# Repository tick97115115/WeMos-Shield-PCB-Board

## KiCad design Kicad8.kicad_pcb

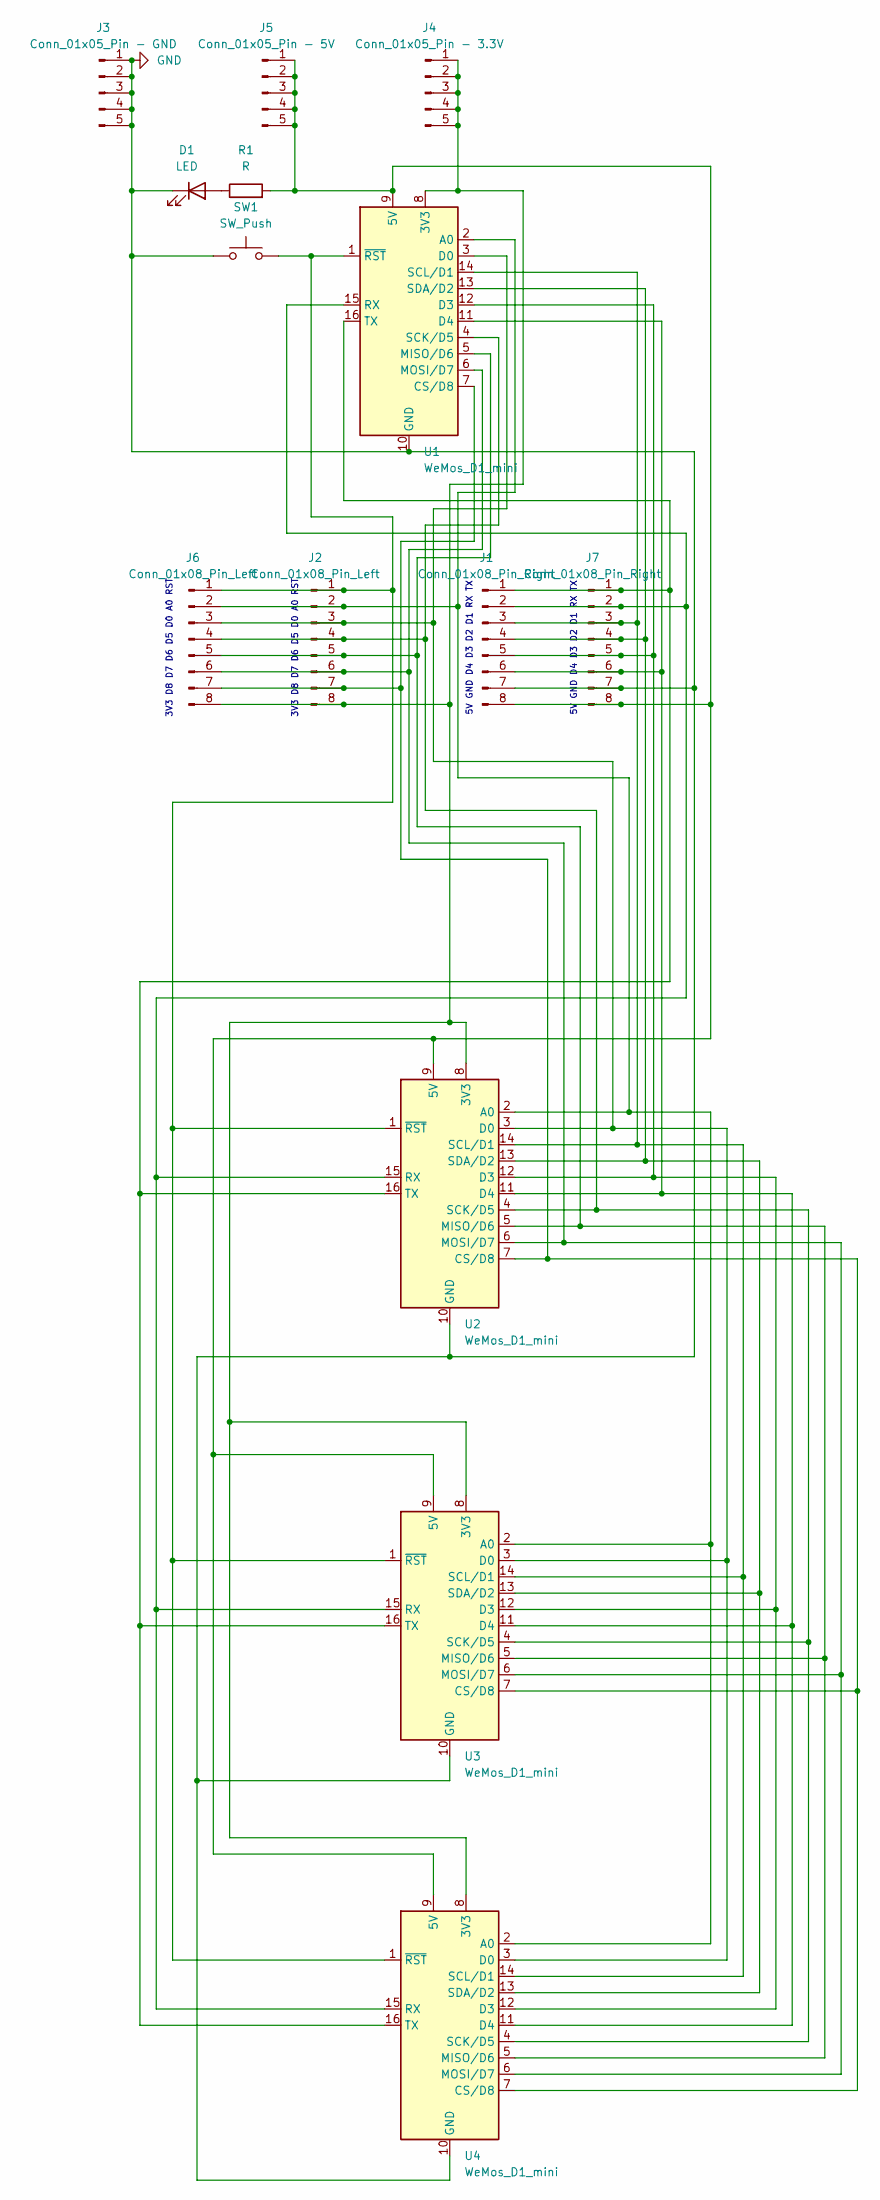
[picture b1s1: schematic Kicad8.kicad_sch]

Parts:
D1: LED; LED_D3.0mm
J1: Conn_01x08_Pin_Right; PinHeader_1x08_P2.54mm_Vertical
J2: Conn_01x08_Pin_Left; PinHeader_1x08_P2.54mm_Vertical
J3: Conn_01x05_Pin - GND; PinSocket_1x05_P2.54mm_Vertical
J4: Conn_01x05_Pin - 3.3V; PinSocket_1x05_P2.54mm_Vertical
J5: Conn_01x05_Pin - 5V; PinSocket_1x05_P2.54mm_Vertical
J6: Conn_01x08_Pin_Left; TerminalBlock_RND_205-00018_1x08_P5.00mm_Horizontal
J7: Conn_01x08_Pin_Right; TerminalBlock_RND_205-00018_1x08_P5.00mm_Horizontal
R1: R; R_Axial_DIN0207_L6.3mm_D2.5mm_P7.62mm_Horizontal
SW1: SW_Push; SW_PUSH_6mm_H5mm
U1, U2, U3, U4: WeMos_D1_mini; WEMOS_D1_mini_light

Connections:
GND: D1.1 (K), J1.7, J3.1, J3.2, J3.3, J3.4, J3.5, J7.7, SW1.1, U1.10 (GND), U2.10 (GND), U3.10 (GND), U4.10 (GND)
unnamed: D1.2 (A), R1.1
unnamed: J1.1, J7.1, U1.16 (TX), U2.16 (TX), U3.16 (TX), U4.16 (TX)
unnamed: J1.2, J7.2, U1.15 (RX), U2.15 (RX), U3.15 (RX), U4.15 (RX)
unnamed: J1.3, J7.3, U1.14 (SCL/D1), U2.14 (SCL/D1), U3.14 (SCL/D1), U4.14 (SCL/D1)
unnamed: J1.4, J7.4, U1.13 (SDA/D2), U2.13 (SDA/D2), U3.13 (SDA/D2), U4.13 (SDA/D2)
unnamed: J1.5, J7.5, U1.12 (D3), U2.12 (D3), U3.12 (D3), U4.12 (D3)
unnamed: J1.6, J7.6, U1.11 (D4), U2.11 (D4), U3.11 (D4), U4.11 (D4)
unnamed: J1.8, J5.1, J5.2, J5.3, J5.4, J5.5, J7.8, R1.2, U1.9 (5V), U2.9 (5V), U3.9 (5V), U4.9 (5V)
unnamed: J2.1, J6.1, SW1.2, U1.1 (~RST), U2.1 (~RST), U3.1 (~RST), U4.1 (~RST)
unnamed: J2.2, J6.2, U1.2 (A0), U2.2 (A0), U3.2 (A0), U4.2 (A0)
unnamed: J2.3, J6.3, U1.3 (D0), U2.3 (D0), U3.3 (D0), U4.3 (D0)
unnamed: J2.4, J6.4, U1.4 (SCK/D5), U2.4 (SCK/D5), U3.4 (SCK/D5), U4.4 (SCK/D5)
unnamed: J2.5, J6.5, U1.5 (MISO/D6), U2.5 (MISO/D6), U3.5 (MISO/D6), U4.5 (MISO/D6)
unnamed: J2.6, J6.6, U1.6 (MOSI/D7), U2.6 (MOSI/D7), U3.6 (MOSI/D7), U4.6 (MOSI/D7)
unnamed: J2.7, J6.7, U1.7 (CS/D8), U2.7 (CS/D8), U3.7 (CS/D8), U4.7 (CS/D8)
unnamed: J2.8, J4.1, J4.2, J4.3, J4.4, J4.5, J6.8, U1.8 (3V3), U2.8 (3V3), U3.8 (3V3), U4.8 (3V3)

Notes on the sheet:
5V GND D4 D3 D2 D1 RX TX
3V3 D8 D7 D6 D5 D0 A0 RST

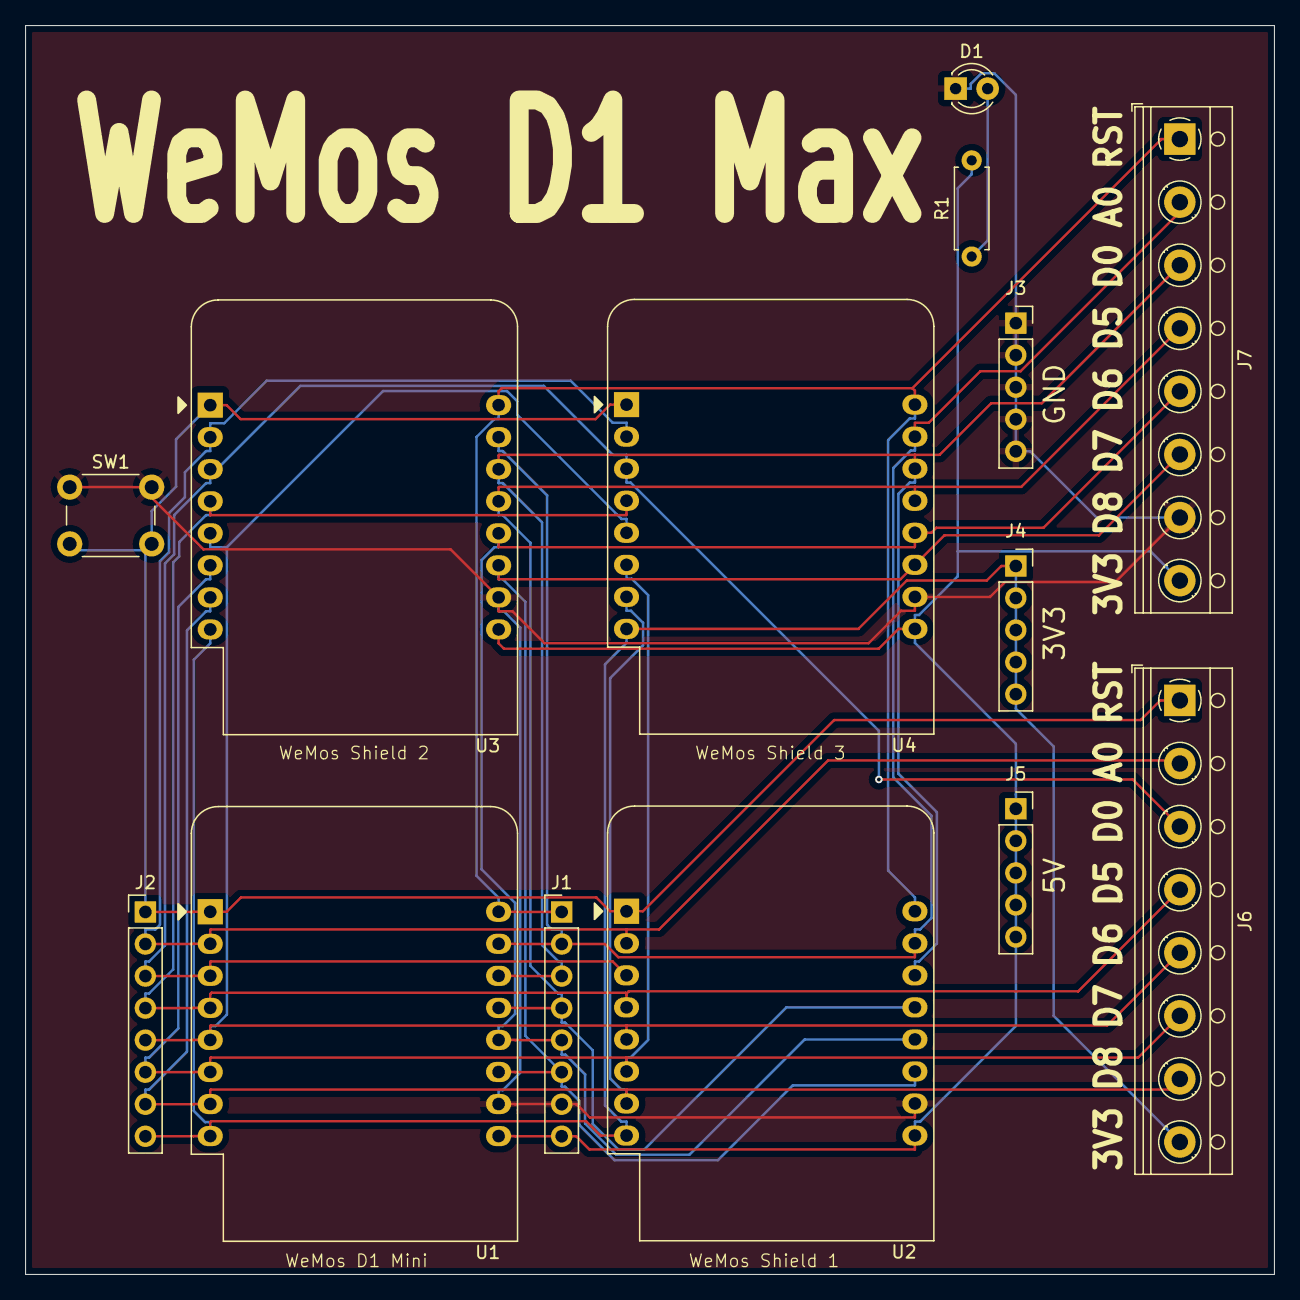
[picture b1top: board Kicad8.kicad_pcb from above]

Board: 2 copper layers, 99.0 x 99.0 mm, 14 parts (0 on the bottom side), 17 nets.

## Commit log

2024-06-30 Init
